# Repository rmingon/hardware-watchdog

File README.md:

# Hardware PCB - LICENCE (CC BY-NC-SA 4.0)

## Based on TPL5010

### For work you will need solder ONE jumper for setting delay of watchdog

### PINOUT 

- VDD - 1.8 to 5.5V
- GND
- DELAY (DLY) - Time Interval set and Manual Reset
- DONE - Logic Input for watchdog functionality
- WAKE - Timer output signal generated every Digital pulsed signal to wake up the µC at the end of tIP period.
- RST - Reset Output (open drain output)

### You can too add your delay with the 'delay' (DLY on silkscreen) see bellow (MORE IN DATASHEET)

#### TODO 
- [X] Add TPL5010
- [X] Add resistor for 100MS
- [X] Add resistor for 500MS
- [X] Add resistor for 1S
- [X] Add resistor for 3S
- [X] Add resistor for 5S

# 3D VIEW

# PCB VIEW

# SCHEMATIC VIEW

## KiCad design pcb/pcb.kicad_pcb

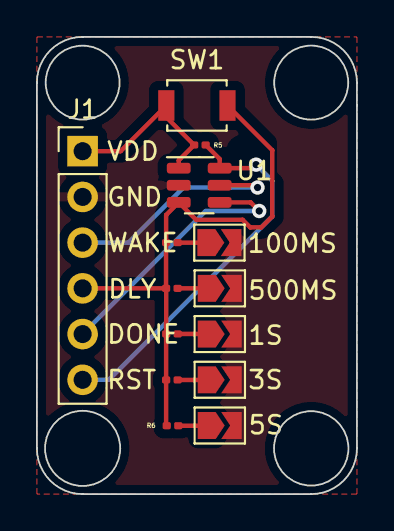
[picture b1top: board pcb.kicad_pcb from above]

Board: 2 copper layers, 17.8 x 25.4 mm, 14 parts (0 on the bottom side), 11 nets.

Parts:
1S: 5.2K; R_0201_0603Metric
3S: 7.628K; R_0201_0603Metric
5S: 8.85K; R_0201_0603Metric
100MS: 500; R_0201_0603Metric
500MS: 2.5K; R_0201_0603Metric
 : Jumper_2_Open; SolderJumper-2_P1.3mm_Open_TrianglePad1.0x1.5mm
J1: Conn_01x06; PinHeader_1x06_P2.54mm_Vertical
JP1, JP2, JP4, JP5: Jumper_2_Open; SolderJumper-2_P1.3mm_Open_TrianglePad1.0x1.5mm
R5: 10K; R_0201_0603Metric
SW1: SW_Push; SW_SPST_B3U-1000P
U1: TPL5010; SOT-23-6

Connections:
DELAY/M_RST: 1S.1, 3S.1, 5S.1, 100MS.1, 500MS.1, J1.4, SW1.1, U1.3 (DELAY/M_RST)
DONE: J1.5, U1.4 (DONE)
GND: .2 (B), J1.2, JP1.2 (B), JP2.2 (B), JP4.2 (B), JP5.2 (B), U1.2 (GND)
unnamed: 100MS.2, JP1.1 (A)
unnamed: 500MS.2, JP2.1 (A)
unnamed: 1S.2, .1 (A)
unnamed: 3S.2, JP4.1 (A)
unnamed: 5S.2, JP5.1 (A)
RST: J1.6, R5.2, U1.6 (~RST)
VDD: J1.1, R5.1, SW1.2, U1.1 (VDD)
WAKE: J1.3, U1.5 (WAKE)

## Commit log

2023-02-09 add pcb
2023-02-09 add gitignore
2023-02-09 add pcb img
2023-02-09 add readme
2023-02-09 edit readme
2023-02-09 add delay
2023-02-09 add datasheet
2023-02-09 add delay info
2023-02-09 add licence + pinout info
